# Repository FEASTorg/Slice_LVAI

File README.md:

# Low-Voltage Analog Input Reader Slice

Low-Voltage Analog Input Reader Slice for BREAD.

## Introduction

[Short introduction on the project.]

## Usage

[Explain how to use the project. Include examples and screenshots if applicable.]

## Documentation 

Please refer to the [docs](/docs) for more info.

---

<div align="center">
  
</div>

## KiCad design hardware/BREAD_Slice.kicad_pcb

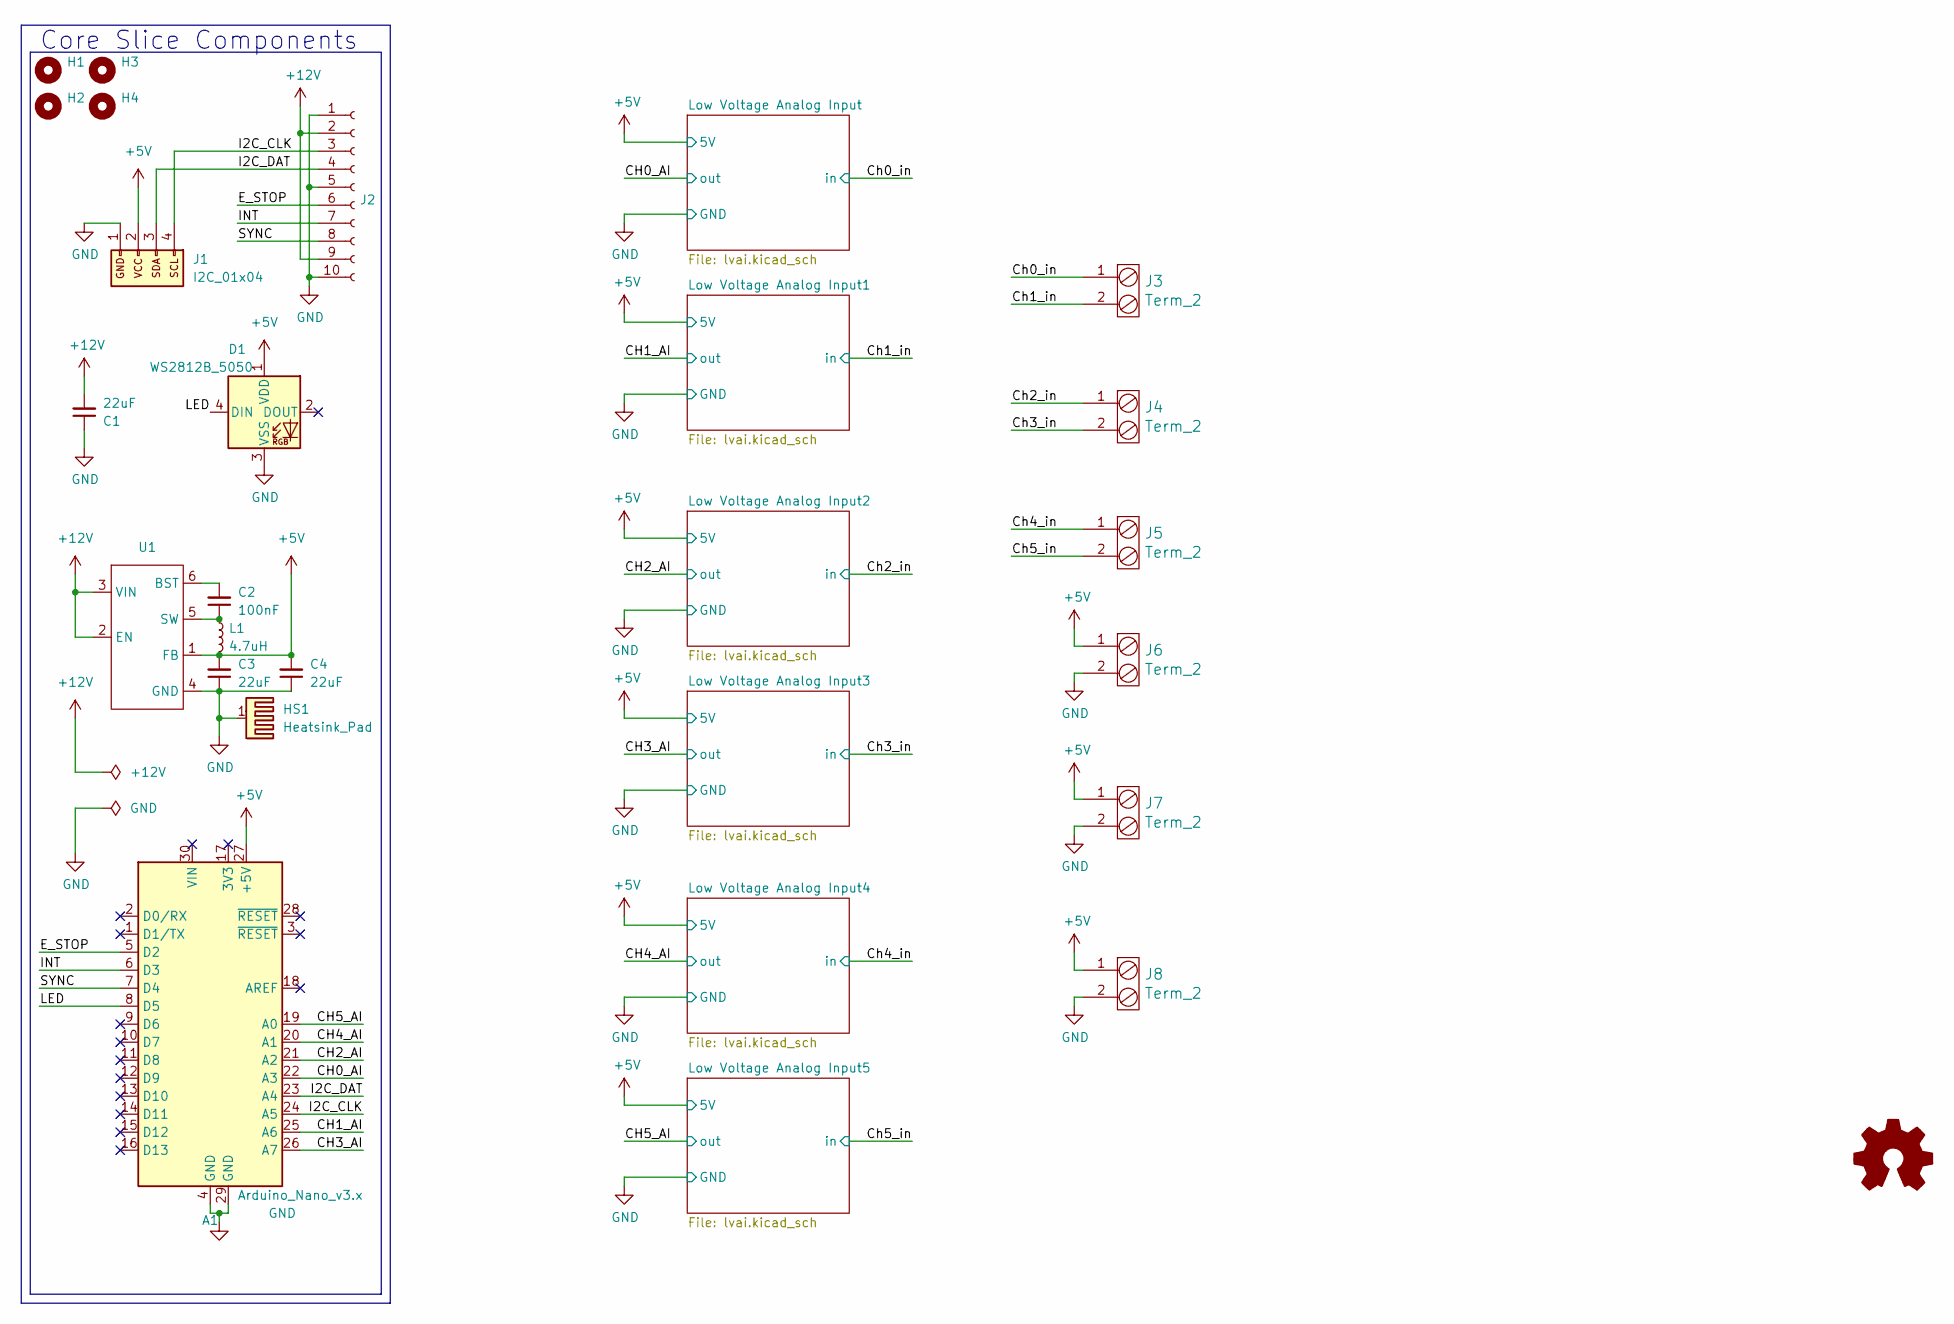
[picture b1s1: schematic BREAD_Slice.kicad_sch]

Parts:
A1: Arduino_Nano_v3.x; Arduino_Nano
C1, C3, C4: 22uF; C_1206_3216Metric
C2: 100nF; C_1206_3216Metric
D1: WS2812B_5050; WS2812-5050-4PIN
H1, H2, H3, H4: MountingHole; MountingHole_5mm
HS1: Heatsink_Pad; Thermal Pad
J1: I2C_01x04; JST_SH_SM04B-SRSS-TB_1x04-1MP_P1.00mm_Horizontal
J2: Conn_01x10_Female; PinSocket_1x10_P2.54mm_Horizontal
J3, J4, J5, J6, J7, J8: Term_2; TerminalBlock_Phoenix_MKDS-1,5-2_1x02_P5.00mm_Horizontal; Part # 1935161
L1: 4.7uH; L_1210_3225Metric
U1: TSOT-23-6

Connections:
+5V: A1.27 (+5V), C3.2, C4.2, D1.1 (VDD), J1.2, J6.1, J7.1, J8.1, L1.2, U1.1 (FB); also elsewhere on the board
+12V: C1.2, J2.2, J2.9, U1.2 (EN), U1.3 (VIN)
/CH0_AI: A1.22 (A3); also elsewhere on the board
/CH1_AI: A1.25 (A6); also elsewhere on the board
/CH2_AI: A1.21 (A2); also elsewhere on the board
/CH3_AI: A1.26 (A7); also elsewhere on the board
/CH4_AI: A1.20 (A1); also elsewhere on the board
/CH5_AI: A1.19 (A0); also elsewhere on the board
/Ch0_in: J3.1; also elsewhere on the board
/Ch1_in: J3.2; also elsewhere on the board
/Ch2_in: J4.1; also elsewhere on the board
/Ch3_in: J4.2; also elsewhere on the board
/Ch4_in: J5.1; also elsewhere on the board
/Ch5_in: J5.2; also elsewhere on the board
/E_STOP: A1.5 (D2), J2.6
/I2C_CLK: A1.24 (A5), J1.4, J2.3
/I2C_DAT: A1.23 (A4), J1.3, J2.4
/INT: A1.6 (D3), J2.7
/LED: A1.8 (D5), D1.4 (DIN)
/SYNC: A1.7 (D4), J2.8
GND: A1.4 (GND), A1.29 (GND), C1.1, C3.1, C4.1, D1.3 (VSS), HS1.1, J1.1, J2.1, J2.5, J2.10, J6.2, J7.2, J8.2, U1.4 (GND); also elsewhere on the board
unnamed: C2.2, U1.6 (BST)
unnamed: C2.1, L1.1, U1.5 (SW)

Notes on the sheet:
Core Slice Components

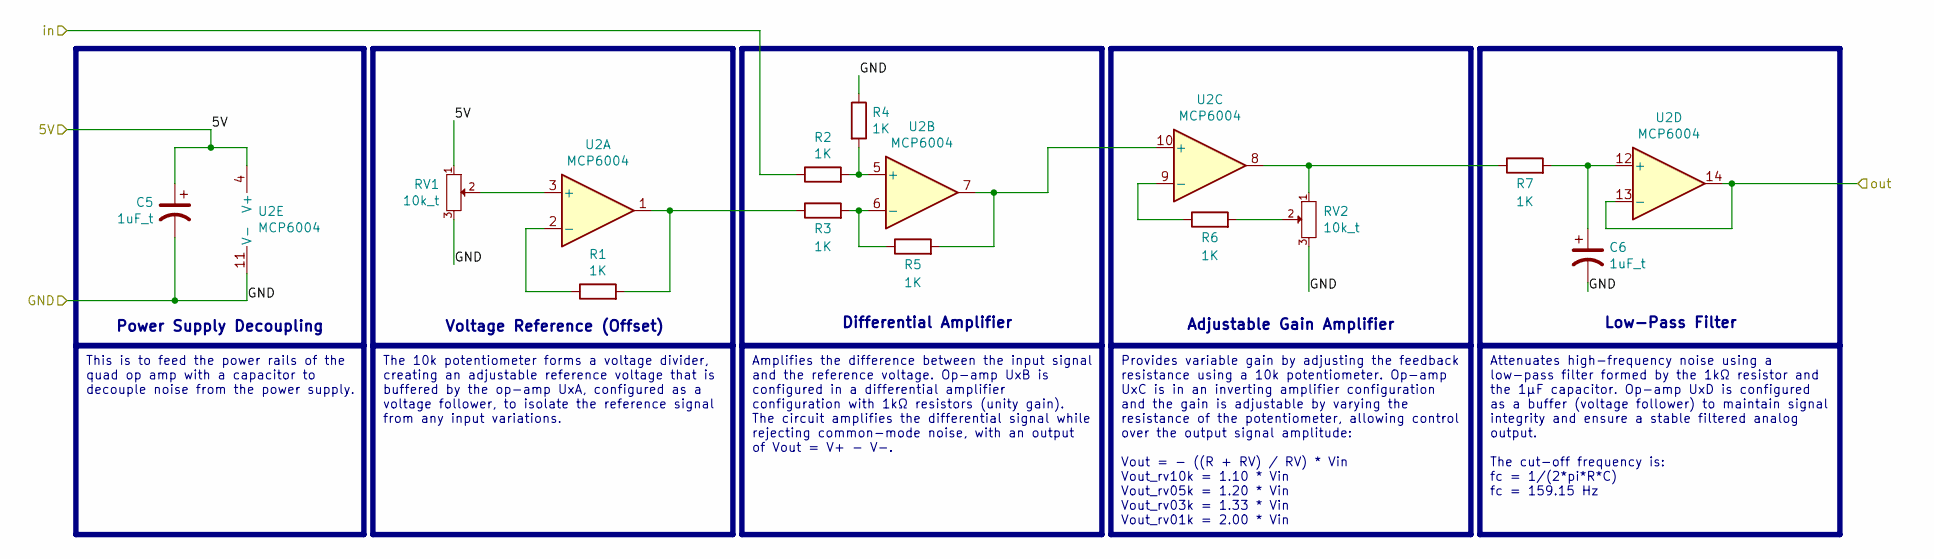
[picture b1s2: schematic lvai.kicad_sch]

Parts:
C5, C6: 1uF_t; C_1206_3216Metric_Pad1.33x1.80mm_HandSolder; Part # T491A105K025AT
R1, R2, R3, R4, R5, R6, R7: 1K; R_1206_3216Metric_Pad1.30x1.75mm_HandSolder; Part # RC1206FR-071KL
RV1, RV2: 10k_t; Potentiometer_Bourns_3296W_Vertical; Part # 1-1623849-0
U2: MCP6004; DIP-14_W7.62mm_Socket_LongPads

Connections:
+5V: C5.1, RV1.1, U2.4 (V+); also elsewhere on the board
/CH0_AI: U2.13 (-), U2.14; also elsewhere on the board
/Ch0_in: R2.1; also elsewhere on the board
GND: C5.2, C6.2, R4.1, RV1.3, RV2.3, U2.11 (V-); also elsewhere on the board
unnamed: R1.2, R3.1, U2.1
unnamed: R6.2, RV2.2
unnamed: R7.1, RV2.1, U2.8
unnamed: RV1.2, U2.3 (+)
unnamed: R1.1, U2.2 (-)
unnamed: R2.2, R4.2, U2.5 (+)
unnamed: R3.2, R5.1, U2.6 (-)
unnamed: R5.2, U2.7, U2.10 (+)
unnamed: R6.1, U2.9 (-)
unnamed: C6.1, R7.2, U2.12 (+)

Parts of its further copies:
C7, C8, C9, C10, C11, C12, C13, C14, C15, C16: 1uF_t; C_1206_3216Metric_Pad1.33x1.80mm_HandSolder; Part # T491A105K025AT
R8, R9, R10, R11, R12, R13, R14, R15, R16, R17, R18, R19, R20, R21, R22, R23, R24, R25, R26, R27, R28, R29, R30, R31, R32, R33, R34, R35, R36, R37, R38, R39, R40, R41, R42: 1K; R_1206_3216Metric_Pad1.30x1.75mm_HandSolder; Part # RC1206FR-071KL
RV3, RV4, RV5, RV6, RV7, RV8, RV9, RV10, RV11, RV12: 10k_t; Potentiometer_Bourns_3296W_Vertical; Part # 1-1623849-0
U3, U4, U5, U6, U7: MCP6004; DIP-14_W7.62mm_Socket_LongPads

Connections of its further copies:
+5V: C7.1, C9.1, C11.1, C13.1, C15.1, RV3.1, RV5.1, RV7.1, RV9.1, RV11.1, U3.4 (V+), U4.4 (V+), U5.4 (V+), U6.4 (V+), U7.4 (V+); also elsewhere on the board
/CH1_AI: U3.13 (-), U3.14; also elsewhere on the board
/CH2_AI: U4.13 (-), U4.14; also elsewhere on the board
/CH3_AI: U5.13 (-), U5.14; also elsewhere on the board
/CH4_AI: U6.13 (-), U6.14; also elsewhere on the board
/CH5_AI: U7.13 (-), U7.14; also elsewhere on the board
/Ch1_in: R9.1; also elsewhere on the board
/Ch2_in: R16.1; also elsewhere on the board
/Ch3_in: R23.1; also elsewhere on the board
/Ch4_in: R30.1; also elsewhere on the board
/Ch5_in: R37.1; also elsewhere on the board
GND: C7.2, C8.2, C9.2, C10.2, C11.2, C12.2, C13.2, C14.2, C15.2, C16.2, R11.1, R18.1, R25.1, R32.1, R39.1, RV3.3, RV4.3, RV5.3, RV6.3, RV7.3, RV8.3, RV9.3, RV10.3, RV11.3, RV12.3, U3.11 (V-), U4.11 (V-), U5.11 (V-), U6.11 (V-), U7.11 (V-); also elsewhere on the board
unnamed: R8.2, R10.1, U3.1
unnamed: R13.2, RV4.2
unnamed: R14.1, RV4.1, U3.8
unnamed: R15.2, R17.1, U4.1
unnamed: R20.2, RV6.2
unnamed: R21.1, RV6.1, U4.8
unnamed: R22.2, R24.1, U5.1
unnamed: R27.2, RV8.2
unnamed: R28.1, RV8.1, U5.8
unnamed: R29.2, R31.1, U6.1
unnamed: R34.2, RV10.2
unnamed: R35.1, RV10.1, U6.8
unnamed: R36.2, R38.1, U7.1
unnamed: R41.2, RV12.2
unnamed: R42.1, RV12.1, U7.8
unnamed: RV3.2, U3.3 (+)
unnamed: R8.1, U3.2 (-)
unnamed: R9.2, R11.2, U3.5 (+)
unnamed: R10.2, R12.1, U3.6 (-)
unnamed: R12.2, U3.7, U3.10 (+)
unnamed: R13.1, U3.9 (-)
unnamed: C8.1, R14.2, U3.12 (+)
unnamed: RV5.2, U4.3 (+)
unnamed: R15.1, U4.2 (-)
unnamed: R16.2, R18.2, U4.5 (+)
unnamed: R17.2, R19.1, U4.6 (-)
unnamed: R19.2, U4.7, U4.10 (+)
unnamed: R20.1, U4.9 (-)
unnamed: C10.1, R21.2, U4.12 (+)
unnamed: RV7.2, U5.3 (+)
unnamed: R22.1, U5.2 (-)
unnamed: R23.2, R25.2, U5.5 (+)
unnamed: R24.2, R26.1, U5.6 (-)
unnamed: R26.2, U5.7, U5.10 (+)
unnamed: R27.1, U5.9 (-)
unnamed: C12.1, R28.2, U5.12 (+)
unnamed: RV9.2, U6.3 (+)
unnamed: R29.1, U6.2 (-)
unnamed: R30.2, R32.2, U6.5 (+)
unnamed: R31.2, R33.1, U6.6 (-)
unnamed: R33.2, U6.7, U6.10 (+)
unnamed: R34.1, U6.9 (-)
unnamed: C14.1, R35.2, U6.12 (+)
unnamed: RV11.2, U7.3 (+)
unnamed: R36.1, U7.2 (-)
unnamed: R37.2, R39.2, U7.5 (+)
unnamed: R38.2, R40.1, U7.6 (-)
unnamed: R40.2, U7.7, U7.10 (+)
unnamed: R41.1, U7.9 (-)
unnamed: C16.1, R42.2, U7.12 (+)

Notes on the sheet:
Voltage Reference (Offset)
Differential Amplifier
Power Supply Decoupling
Low-Pass Filter
Adjustable Gain Amplifier
The 10k potentiometer forms a voltage divider, creating an adjustable reference voltage that is buffered by the op-amp UxA, configured as a voltage follower, to isolate the reference signal from any input variations.
Provides variable gain by adjusting the feedback resistance using a 10k potentiometer. Op-amp UxC is in an inverting amplifier configuration and the gain is adjustable by varying the resistance of the potentiometer, allowing control over the output signal amplitude: Vout = - ((R + RV) / RV) * Vin V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
This is to feed the power rails of the quad op amp with a capacitor to decouple noise from the power supply.
Attenuates high-frequency noise using a low-pass filter formed by the 1kΩ resistor and the 1μF capacitor. Op-amp UxD is configured as a buffer (voltage follower) to maintain signal integrity and ensure a stable filtered analog output. The cut-off frequency is: fc = 1/(2*pi*R*C) fc = 159.15 Hz
Amplifies the difference between the input signal and the reference voltage. Op-amp UxB is configured in a differential amplifier configuration with 1kΩ resistors (unity gain). The circuit amplifies the differential signal while rejecting common-mode noise, with an output of Vout = V+ - V-.

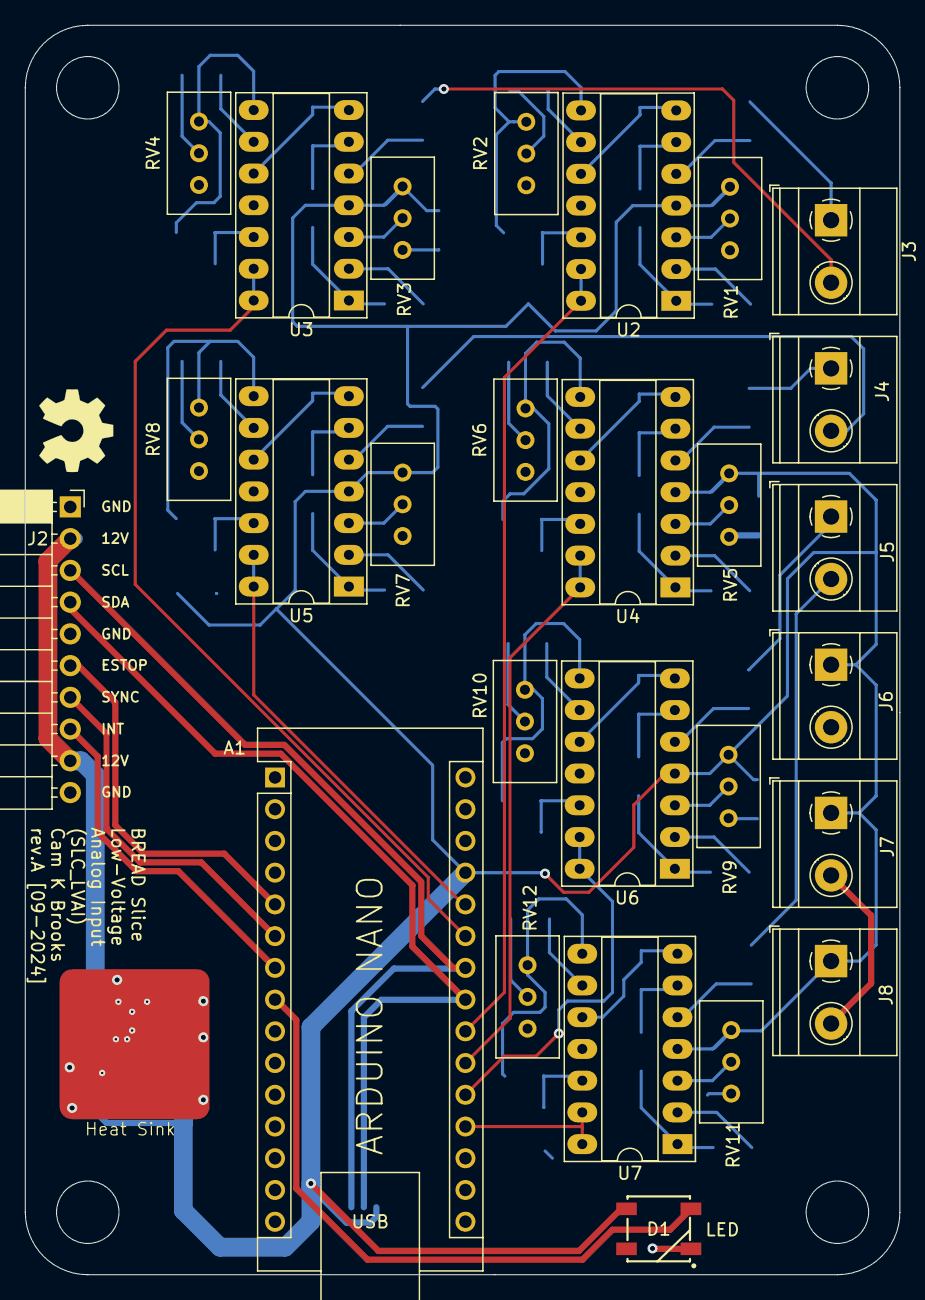
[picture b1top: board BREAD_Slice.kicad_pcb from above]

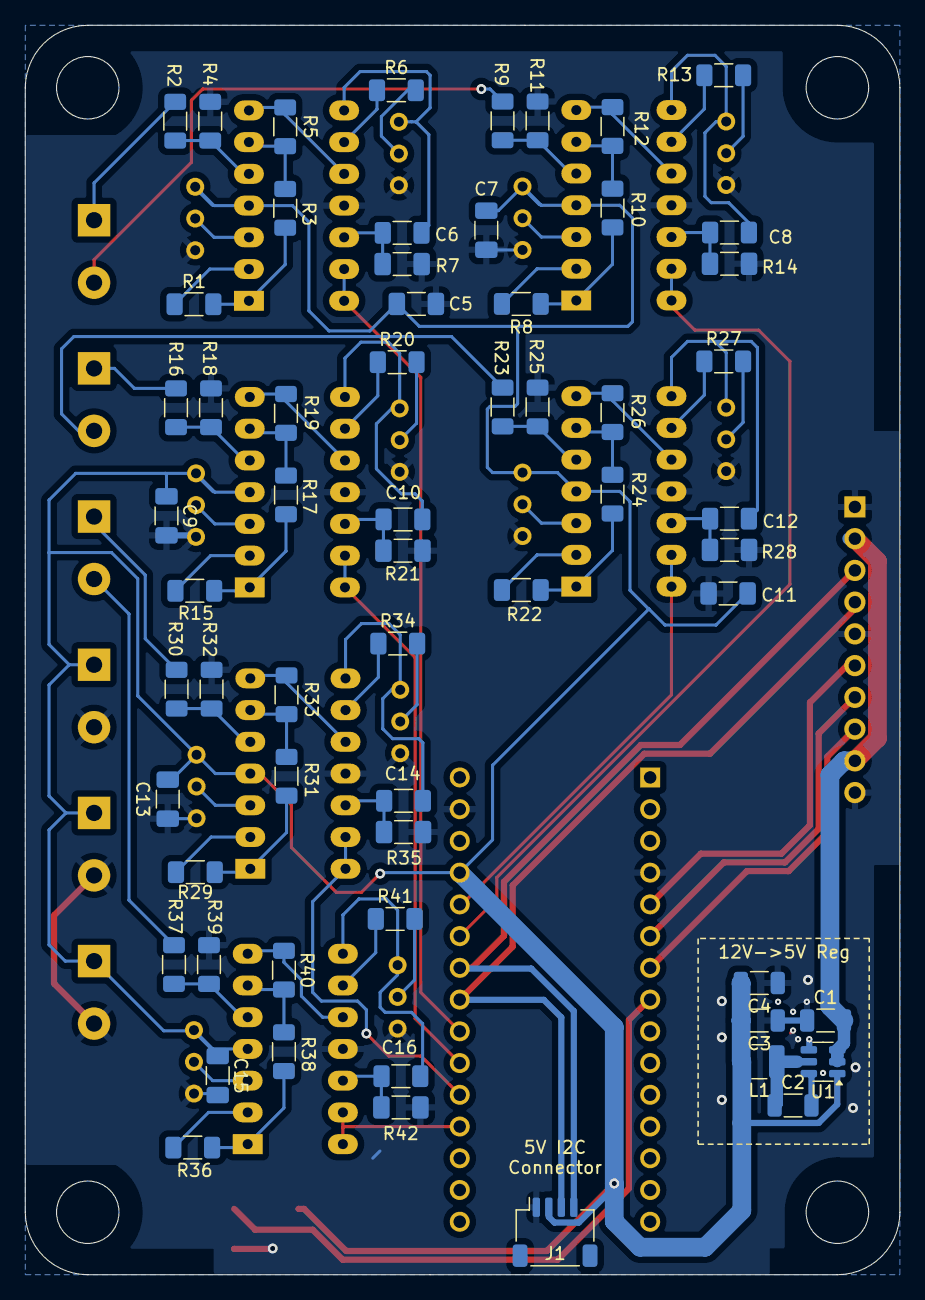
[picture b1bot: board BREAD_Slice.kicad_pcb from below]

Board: 2 copper layers, 70.0 x 100.0 mm, 94 parts (61 on the bottom side), 83 nets.

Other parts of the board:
Logo1: Logo_Open_Hardware_Small; OSHW-Symbol_6.7x6mm_SilkScreen

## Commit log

2024-09-10 set repo
2024-09-12 extensive documentation, remade board, subcircuits for all
2024-09-30 JLCPCB order rev-A
2026-04-18 chore: minor updates
2026-05-20 Add slice.yaml manifest (schema v1.0)
2026-05-24 Add KiBot/docs pipeline
2026-05-24 📄 KiBot index + board renders (auto)
2026-05-24 TODO: all CI green
2026-05-24 Standardize TODO.md with Pass 1/Pass 2 structure
